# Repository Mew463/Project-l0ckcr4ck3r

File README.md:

# Project-l0ckcr4ck3r
This robot is a true creation of the idea many years ago brought on by [Samy Kamkar's robot](https://samy.pl/combobreaker/) that "utilized" his algorithm for cracking combination locks. Samy Kamkar never demonstrated his robot actually performing the algorithm, though he implied multiple times that it does do it.

I've always wanted to build a robot that actually decodes locks while maintaining a cool desk toy vibe! I am quite happy with the user-oriented design and doubles as a nice fidgety-toy-thing to play with.  

This robot is able to decode the majority of locks that don't have much wear and tear on it and usually takes ~40 seconds.

<br/><br/>

## Photo

## Video

# How it works. 
## Cracking lock Algorithm 
First number: Turn dial Counter Clockwise while incrementally adding more and more force to the shackle until it suddenly stops. Round down to the nearest whole number and add 14. That is the first number in the combo. 

Third number: 
1) Find the gates between digits 0 - 10 . 
2) Take the two gates that correspond to a whole number and see whether each of those numbers %(modulo) 4 = firstNum % 4. 
3) If the equation is satisfied, store that number somewhere. Now add 10 to each number and perform the same operation as the previous step until you have **two** numbers that satisfy the equation
4) Now check the gate size of the two numbers which satisfy the equation. The number with the biggest gate is the third number. 

Second number: Guess and check until the lock opens, though it follows a pattern of being (FirstNum % 4) + a multiple of 4.

I found that this [video](https://www.youtube.com/watch?v=27rE5ZvWLU0&ab_channel=HelpfulLockPicker) really helped me when trying to program the algorithm.

## This robot 
A TMC2208 Trinamic driver drives a stepper motor & magnetic encoder. These components turn the dial and can detect when the stepper motor stalls. 

With this method, any desired number can easily be input into the lock and the lock can be "felt" for it's geometries.

Meanwhile a servo powers a rack and pinion gear which allows precise control of the shackle.

Since I modified the servo with an [analog Feedback wire](https://www.youtube.com/watch?v=XfZLtkr6dgU&ab_channel=CuriousMotor), we can pull up on the shackle and use this to check whether the lock has been opened or not. 

# 3D Model

[CAD Files](https://cad.onshape.com/documents/2b977856993104d0f24f1470/w/e2828f2601c6a316a05788e0/e/a76e54aa91df89bb32ae0012)

# Electronics 
Custom PCB powered by a 12V USB C input. An Arduino Nano is the brain and a 5V regulator gives the neccessary voltage for the servo. 

KiCAD files are included in the github. 

# Materials

## Mechanical
* [TMC2208 Stepper Driver](https://www.amazon.com/Printer-TMC2208-Screwdriver-Controller-Ramps1-4/dp/B082LSQWZF/ref=sr_1_3?crid=2DM8J6G3IDA8J&keywords=tmc2208&qid=1661839331&sprefix=tmc2208%2Caps%2C133&sr=8-3)
* [High torque servos](https://www.amazon.com/Youleke-Torque-Digital-Servo%EF%BC%8CWaterproof-Horn%EF%BC%88270%C2%B0%EF%BC%89/dp/B08739MGPL/ref=sr_1_11?crid=81HZZ5JLGLML&keywords=servo&qid=1661839358&sprefix=servo+%2Caps%2C248&sr=8-11)
* [Stepper motor](https://www.amazon.com/STEPPERONLINE-Bipolar-Stepper-22-6oz-Extruder/dp/B00PNEQ79Q/ref=sr_1_6?crid=1U1NH4LQTF0ZK&keywords=stepper+motor&qid=1661839383&sprefix=stepper+motor+%2Caps%2C139&sr=8-6)
* [AS5600 Magnetic Encoder](https://www.amazon.com/Magnetic-Encoder-Induction-Measurement-Precision/dp/B094F8H591/ref=sr_1_4?crid=M8OANSRLFX5C&keywords=as5600+encoder&qid=1661839450&sprefix=as5600+encod%2Caps%2C130&sr=8-4)
* Assorted M3 Bolts

## Electrical
* Arduino Nano
* 10uF Capacitor x2
* Diode 
* [5V Regulator](https://www.digikey.com/en/products/detail/stmicroelectronics/LD1085V50/669220?s=N4IgTCBcDaIDIBECMAGAHAVgGoZSAugL5A)
* [OLED Display](https://www.amazon.com/Self-Luminous-Display-Compatible-Arduino-Raspberry/dp/B09JWN8K99/ref=sr_1_2_sspa?crid=DM9HX86FS3Q5&keywords=oled+arduino&qid=1661839948&sprefix=oledarduino%2Caps%2C143&sr=8-2-spons&psc=1)
* [Rotary Encoder](https://www.amazon.com/Taiss-KY-040-Encoder-15%C3%9716-5-Arduino/dp/B07F26CT6B/ref=sr_1_4?keywords=rotary+encoder&qid=1661839976&sprefix=roataray%2Caps%2C139&sr=8-4)
* [Blower Fan](https://www.amazon.com/WINSINN-Bearings-Brushless-Cooling-40mm20mm/dp/B08R9JJZ5Z/ref=sr_1_8?crid=1UCHGY2B410VX&keywords=blower+fan+12v+40mm&qid=1661839541&sprefix=blower+fan+12v+40m%2Caps%2C119&sr=8-8)
* [USB C 12V ](https://www.amazon.com/MELIFE-Type-C-Voltage-Trigger-Module/dp/B0953G14Q2/ref=sr_1_3?crid=12XVP47XQI63X&keywords=usb+c+12v+trigger&qid=1662871099&sprefix=usb+c+12v+trigge%2Caps%2C227&sr=8-3)
* [Power Supply](https://www.amazon.com/ZMI-zPower-Turbo-Power-Adapter/dp/B07D64QLQ1/ref=sr_1_5?crid=3I0WTX44C53G1&keywords=usb+c+charger+pd&qid=1662871140&sprefix=usb+c+charger+%2Caps%2C244&sr=8-5)

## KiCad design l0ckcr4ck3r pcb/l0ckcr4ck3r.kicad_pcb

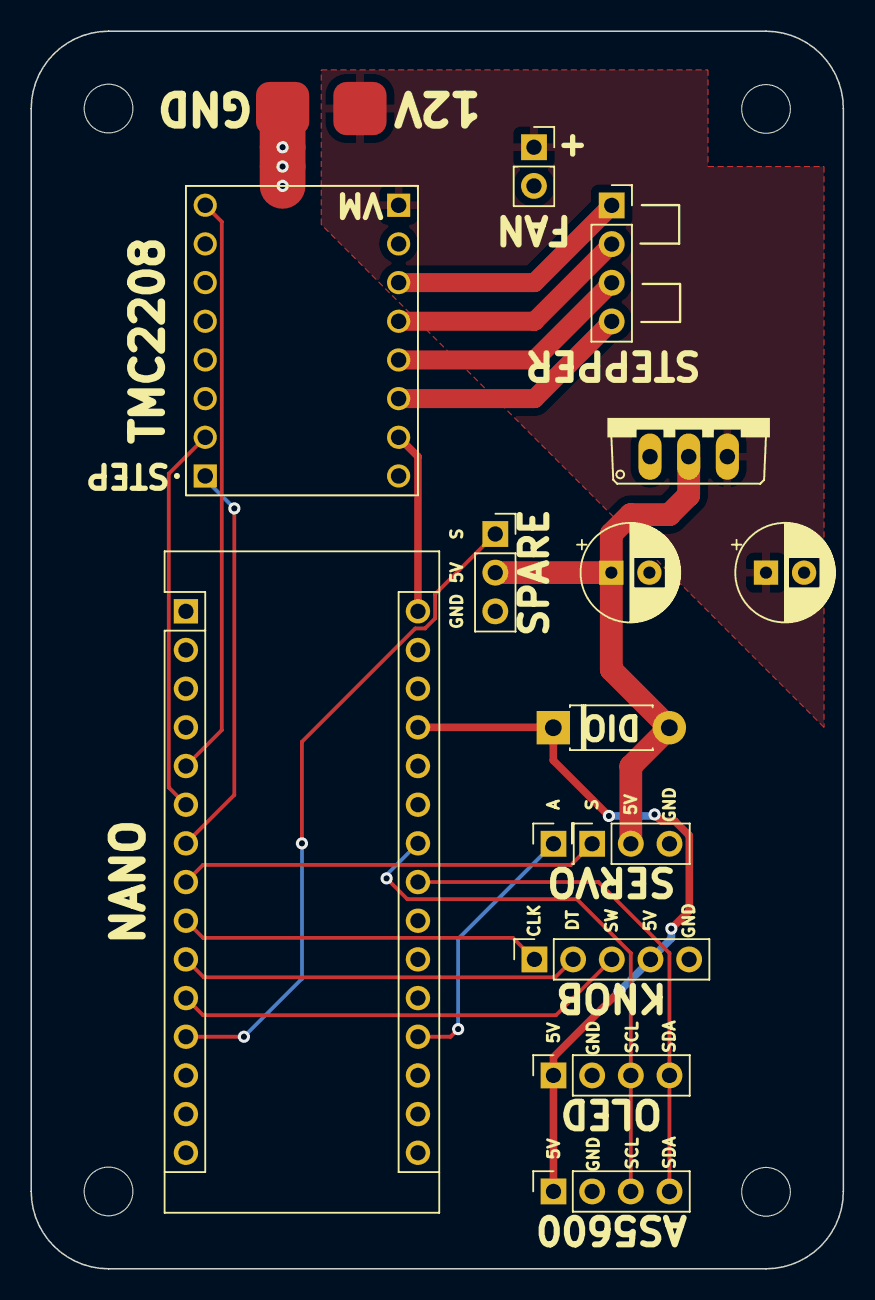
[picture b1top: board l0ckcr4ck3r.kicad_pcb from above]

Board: 2 copper layers, 53.3 x 81.3 mm, 15 parts (0 on the bottom side), 20 nets.

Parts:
A1: Arduino_Nano_v3.x; Arduino_Nano
C1, C2: 10uF; CP_Radial_D6.3mm_P2.50mm
D1: 1N4002; D_DO-41_SOD81_P7.62mm_Horizontal
J1: Servo Feedback; PinSocket_1x01_P2.54mm_Vertical
M1: Stepper_Motor_bipolar; PinSocket_1x04_P2.54mm_Vertical
M2: Fan; PinSocket_1x02_P2.54mm_Vertical
M3: Motor_Servo; PinSocket_1x03_P2.54mm_Vertical
M4: Spare; PinSocket_1x03_P2.54mm_Vertical
U1: PowerIn; PowerPads
U2: TMC2208_SILENTSTEPSTICK; MODULE_TMC2208_SILENTSTEPSTICK
U3: Encoder; PinSocket_1x05_P2.54mm_Vertical
U4: LD1085V50; TO220V
U5: AS5600; PinSocket_1x04_P2.54mm_Vertical
U6: OLED Display; PinSocket_1x04_P2.54mm_Vertical

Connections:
+5V: A1.27 (+5V), D1.1 (K), U3.4 (+), U5.1 (VCC), U6.1 (VCC)
+12V: C2.1, M2.1 (+), U1.1 (12V), U2.JP2_1 (VM), U4.3 (Input)
CLK: A1.9 (D6), U3.1 (CLK)
D5: A1.8 (D5), M3.1 (PWM)
D9: A1.12 (D9), M4.1 (PWM)
DT: A1.10 (D7), U3.2 (DT)
GND: A1.4 (GND), A1.29 (GND), C1.2, C2.2, M2.2 (-), M3.3 (-), M4.3 (-), U1.2 (GND), U2.JP2_2 (GND), U2.JP2_8 (GND), U3.5 (GND), U4.1, U5.2 (GND), U6.2 (GND)
unnamed: A1.5 (D2), U2.JP1_8 (EN)
unnamed: A1.6 (D3), U2.JP1_2 (STEP)
unnamed: A1.7 (D4), U2.JP1_1 (DIR)
unnamed: A1.19 (A0), J1.1
unnamed: A1.30 (VIN), U2.JP2_7 (VIO)
unnamed: C1.1, D1.2 (A), M3.2 (+), M4.2 (+), U4.2
unnamed: M1.1, U2.JP2_3 (OA2)
unnamed: M1.2 (-), U2.JP2_4 (OA1)
unnamed: M1.3, U2.JP2_5 (OB1)
unnamed: M1.4, U2.JP2_6 (OB2)
SCL: A1.24 (A5), U5.3 (SCL), U6.3 (SCL)
SDA: A1.23 (A4), U5.4 (SDA), U6.4 (SDA)
SW: A1.11 (D8), U3.3 (SW)

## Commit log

2022-08-28 intial commit
2022-08-28 first commit gui
2022-08-29 gui working state
2022-09-01 added feedback during lock cracking
2022-09-02 kinda workin, random freezing
2022-09-02 working after reducing memory size
2022-09-02 started on the error case where the start lifting up on a gate for finding third number
2022-09-11 pre take out check twice funcionality
2022-09-11 more debugging, working state
2022-09-15 added kicad and gif
2022-09-15 retry video upload gif
2022-09-17 updated some servo values
2022-09-18 fixed bug with 11-13-39 lock
